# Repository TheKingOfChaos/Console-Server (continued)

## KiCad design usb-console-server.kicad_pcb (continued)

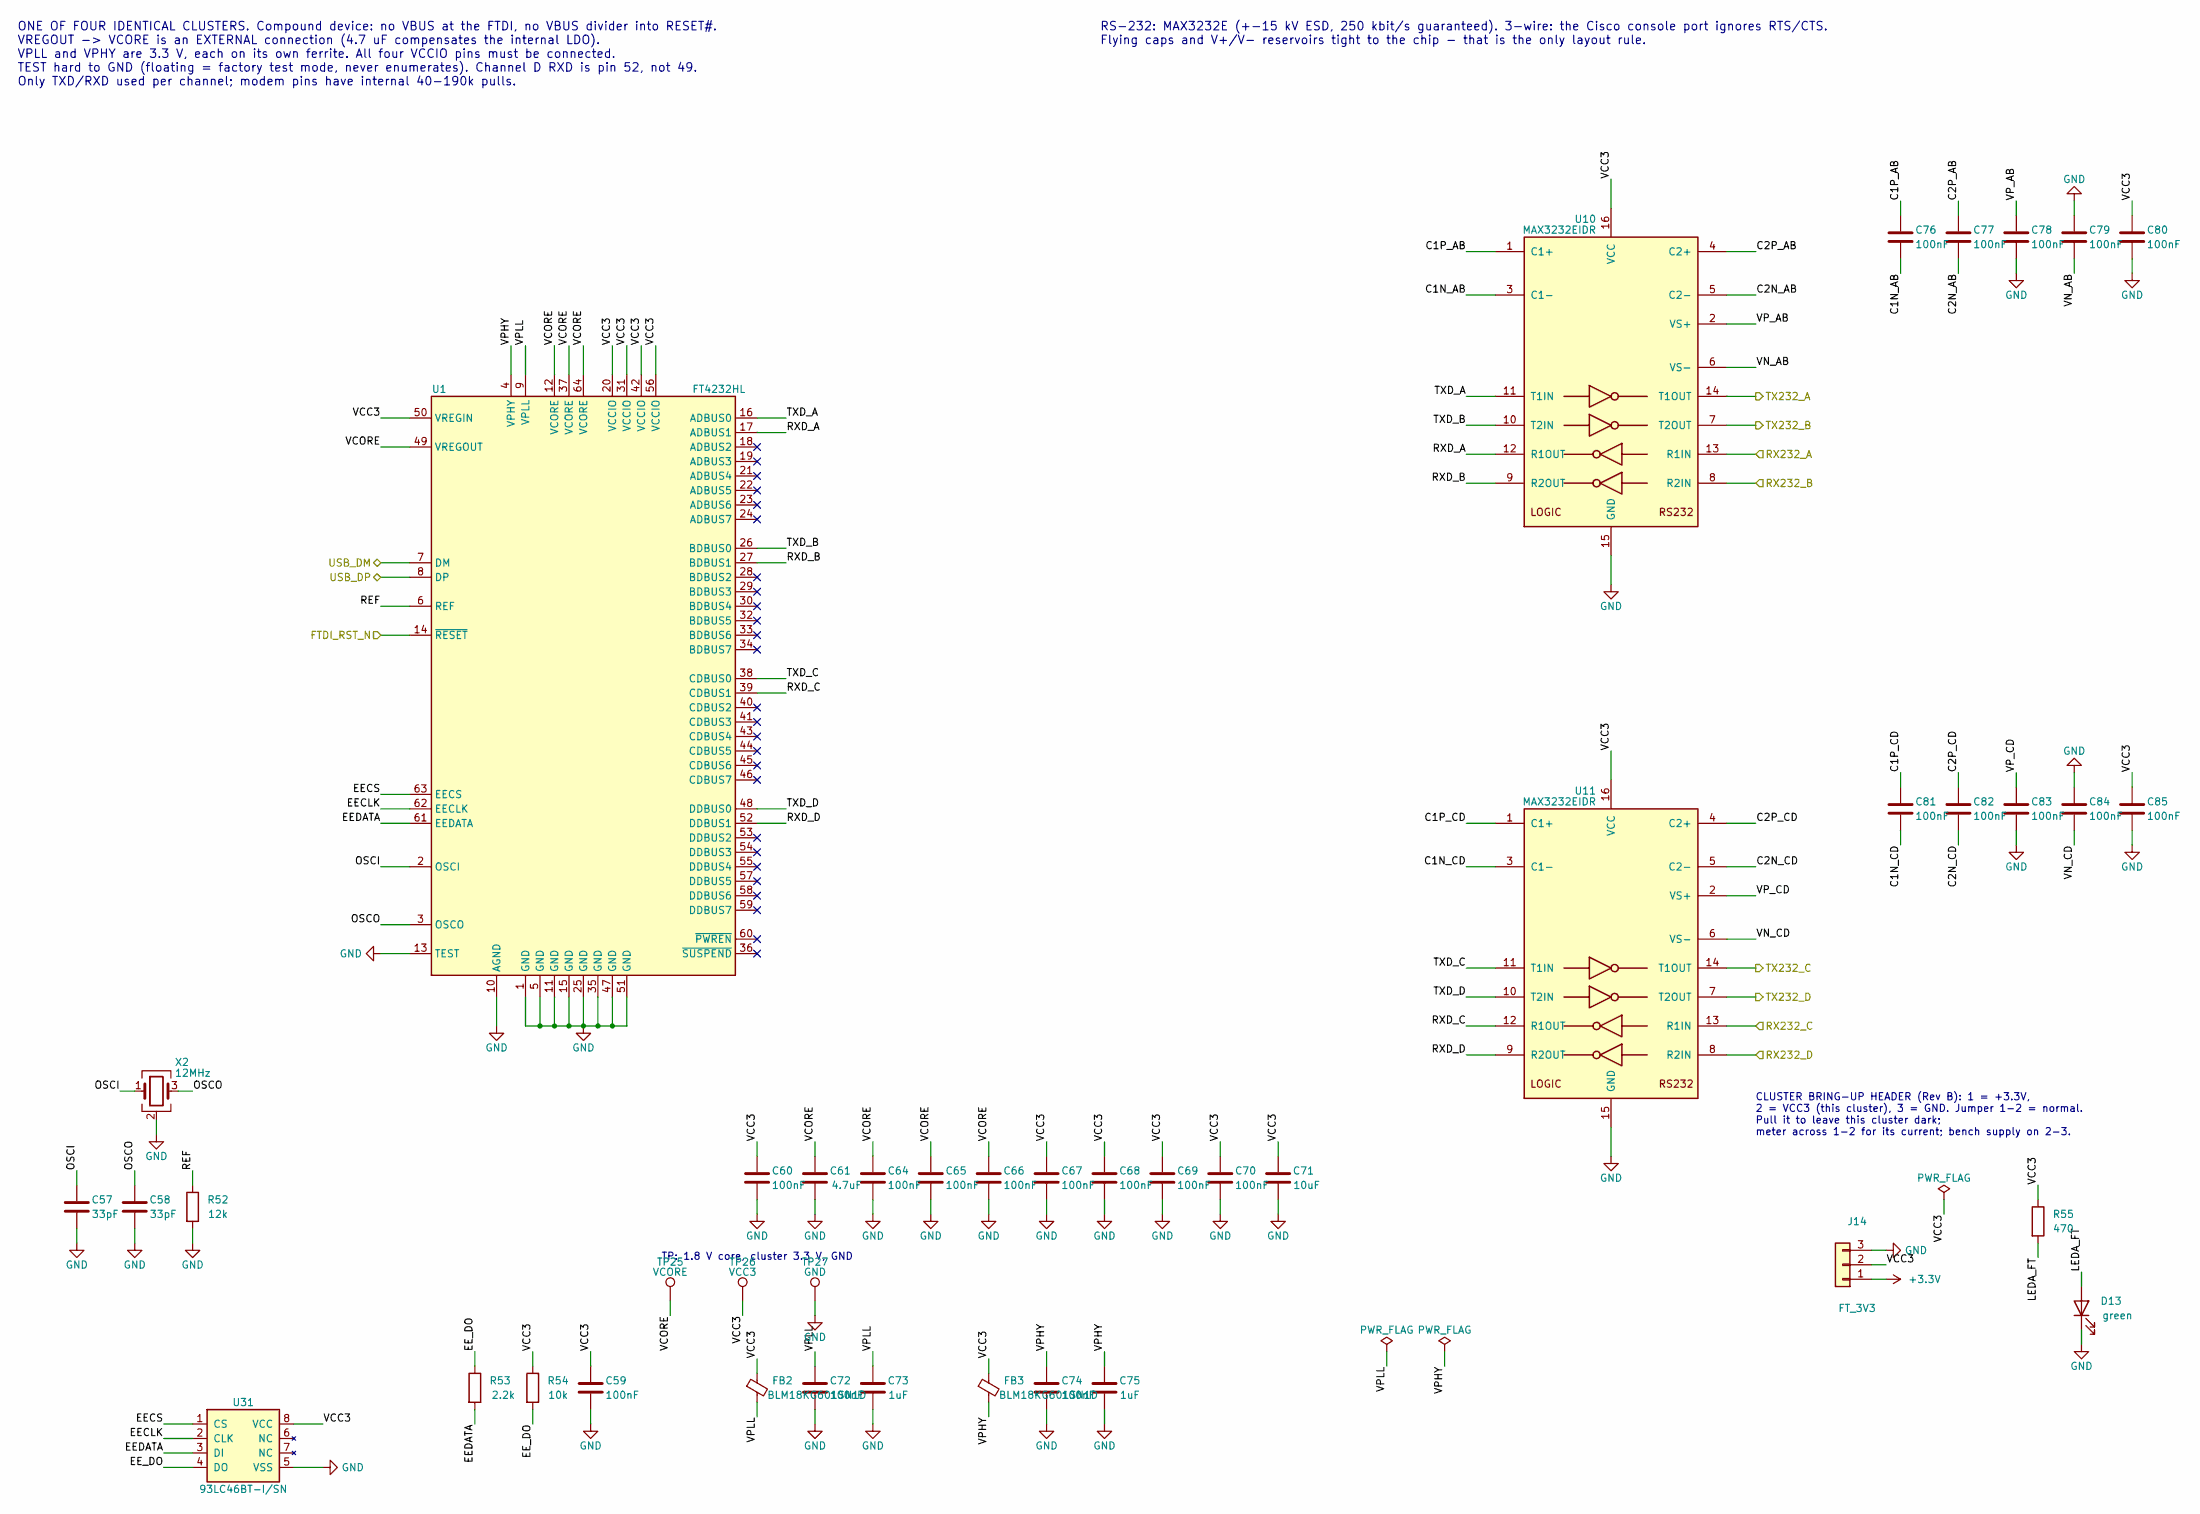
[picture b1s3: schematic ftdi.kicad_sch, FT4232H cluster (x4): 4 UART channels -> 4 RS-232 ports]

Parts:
C57, C58: 33pF; C_0603_1608Metric; LCSC C1663
C59, C60, C64, C65, C66, C67, C68, C69, C70, C72, C74, C76, C77, C78, C79, C80, C81, C82, C83, C84, C85: 100nF; C_0603_1608Metric; LCSC C14663
C61: 4.7uF; C_0805_2012Metric; LCSC C1779
C71: 10uF; C_0805_2012Metric; LCSC C15850
C73, C75: 1uF; C_0603_1608Metric; LCSC C29936
D13: green; LED_0603_1608Metric; LCSC C965805
FB2, FB3: BLM18KG601SN1D; L_0603_1608Metric; LCSC C85833
J14: FT_3V3; PinHeader_1x03_P2.54mm_Vertical; LCSC C49257
R52: 12k; R_0603_1608Metric; LCSC C22790
R53: 2.2k; R_0603_1608Metric; LCSC C4190
R54: 10k; R_0603_1608Metric; LCSC C25804
R55: 470; R_0603_1608Metric; LCSC C23179
TP25: VCORE; TestPoint_Pad_D1.5mm
TP26: VCC3; TestPoint_Pad_D1.5mm
TP27: GND; TestPoint_Pad_D1.5mm
U1: FT4232HL; LQFP-64_10x10mm_P0.5mm; LCSC C56742
U10, U11: MAX3232EIDR; SOIC-16_3.9x9.9mm_P1.27mm; LCSC C193666
U31: 93LC46BT-I/SN; SOIC-8_3.9x4.9mm_P1.27mm; LCSC C16253
X2: 12MHz; Crystal_SMD_3225-4Pin_3.2x2.5mm; LCSC C9002

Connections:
+3.3V: J14.1; also elsewhere on the board
/FT1/C1N_AB: C76.2, U10.3 (C1-)
/FT1/C1N_CD: C81.2, U11.3 (C1-)
/FT1/C1P_AB: C76.1, U10.1 (C1+)
/FT1/C1P_CD: C81.1, U11.1 (C1+)
/FT1/C2N_AB: C77.2, U10.5 (C2-)
/FT1/C2N_CD: C82.2, U11.5 (C2-)
/FT1/C2P_AB: C77.1, U10.4 (C2+)
/FT1/C2P_CD: C82.1, U11.4 (C2+)
/FT1/EECLK: U1.62 (EECLK), U31.2 (CLK)
/FT1/EECS: U1.63 (EECS), U31.1 (CS)
/FT1/EEDATA: R53.2, U1.61 (EEDATA), U31.3 (DI)
/FT1/EE_DO: R53.1, R54.2, U31.4 (DO)
/FT1/LEDA_FT: D13.2 (A), R55.2
/FT1/OSCI: C57.1, U1.2 (OSCI), X2.1
/FT1/OSCO: C58.1, U1.3 (OSCO), X2.3
/FT1/REF: R52.1, U1.6 (REF)
/FT1/RXD_A: U1.17 (ADBUS1), U10.12 (R1OUT)
/FT1/RXD_B: U1.27 (BDBUS1), U10.9 (R2OUT)
/FT1/RXD_C: U1.39 (CDBUS1), U11.12 (R1OUT)
/FT1/RXD_D: U1.52 (DDBUS1), U11.9 (R2OUT)
/FT1/TXD_A: U1.16 (ADBUS0), U10.11 (T1IN)
/FT1/TXD_B: U1.26 (BDBUS0), U10.10 (T2IN)
/FT1/TXD_C: U1.38 (CDBUS0), U11.11 (T1IN)
/FT1/TXD_D: U1.48 (DDBUS0), U11.10 (T2IN)
/FT1/VCC3: C59.1, C60.1, C67.1, C68.1, C69.1, C70.1, C71.1, C80.1, C85.1, FB2.1, FB3.1, J14.2, R54.1, R55.1, TP26.1, U1.20 (VCCIO), U1.31 (VCCIO), U1.42 (VCCIO), U1.50 (VREGIN), U1.56 (VCCIO), U10.16 (VCC), U11.16 (VCC), U31.8 (VCC)
/FT1/VCORE: C61.1, C64.1, C65.1, C66.1, TP25.1, U1.12 (VCORE), U1.37 (VCORE), U1.49 (VREGOUT), U1.64 (VCORE)
/FT1/VN_AB: C79.2, U10.6 (VS-)
/FT1/VN_CD: C84.2, U11.6 (VS-)
/FT1/VPHY: C74.1, C75.1, FB3.2, U1.4 (VPHY)
/FT1/VPLL: C72.1, C73.1, FB2.2, U1.9 (VPLL)
/FT1/VP_AB: C78.1, U10.2 (VS+)
/FT1/VP_CD: C83.1, U11.2 (VS+)
FTDI_RST_N: U1.14 (~RESET); also elsewhere on the board
GND: C57.2, C58.2, C59.2, C60.2, C61.2, C64.2, C65.2, C66.2, C67.2, C68.2, C69.2, C70.2, C71.2, C72.2, C73.2, C74.2, C75.2, C78.2, C79.1, C80.2, C83.2, C84.1, C85.2, D13.1 (K), J14.3, R52.2, TP27.1, U1.1 (GND), U1.5 (GND), U1.10 (AGND), U1.11 (GND), U1.13 (TEST), U1.15 (GND), U1.25 (GND), U1.35 (GND), U1.47 (GND), U1.51 (GND), U10.15 (GND), U11.15 (GND), U31.5 (VSS), X2.2 (G), X2.4 (G); also elsewhere on the board
P01_RXD: U10.13 (R1IN); also elsewhere on the board
P01_TXD: U10.14 (T1OUT); also elsewhere on the board
P02_RXD: U10.8 (R2IN); also elsewhere on the board
P02_TXD: U10.7 (T2OUT); also elsewhere on the board
P03_RXD: U11.13 (R1IN); also elsewhere on the board
P03_TXD: U11.14 (T1OUT); also elsewhere on the board
P04_RXD: U11.8 (R2IN); also elsewhere on the board
P04_TXD: U11.7 (T2OUT); also elsewhere on the board
USB_DN1_DM: U1.7 (DM); also elsewhere on the board
USB_DN1_DP: U1.8 (DP); also elsewhere on the board

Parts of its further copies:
C86, C87, C113, C114, C140, C141: 33pF; C_0603_1608Metric; LCSC C1663
C88, C89, C91, C92, C93, C94, C95, C96, C97, C99, C101, C103, C104, C105, C106, C107, C108, C109, C110, C111, C112, C115, C116, C118, C119, C120, C121, C122, C123, C124, C126, C128, C130, C131, C132, C133, C134, C135, C136, C137, C138, C139, C142, C143, C145, C146, C147, C148, C149, C150, C151, C153, C155, C157, C158, C159, C160, C161, C162, C163, C164, C165, C166: 100nF; C_0603_1608Metric; LCSC C14663
C90, C117, C144: 4.7uF; C_0805_2012Metric; LCSC C1779
C98, C125, C152: 10uF; C_0805_2012Metric; LCSC C15850
C100, C102, C127, C129, C154, C156: 1uF; C_0603_1608Metric; LCSC C29936
D14, D15, D16: green; LED_0603_1608Metric; LCSC C965805
FB4, FB5, FB6, FB7, FB8, FB9: BLM18KG601SN1D; L_0603_1608Metric; LCSC C85833
J15, J16, J17: FT_3V3; PinHeader_1x03_P2.54mm_Vertical; LCSC C49257
R56, R60, R64: 12k; R_0603_1608Metric; LCSC C22790
R57, R61, R65: 2.2k; R_0603_1608Metric; LCSC C4190
R58, R62, R66: 10k; R_0603_1608Metric; LCSC C25804
R59, R63, R67: 470; R_0603_1608Metric; LCSC C23179
TP28, TP31, TP34: VCORE; TestPoint_Pad_D1.5mm
TP29, TP32, TP35: VCC3; TestPoint_Pad_D1.5mm
TP30, TP33, TP36: GND; TestPoint_Pad_D1.5mm
U2, U3, U4: FT4232HL; LQFP-64_10x10mm_P0.5mm; LCSC C56742
U12, U13, U14, U15, U16, U17: MAX3232EIDR; SOIC-16_3.9x9.9mm_P1.27mm; LCSC C193666
U32, U33, U34: 93LC46BT-I/SN; SOIC-8_3.9x4.9mm_P1.27mm; LCSC C16253
X3, X4, X5: 12MHz; Crystal_SMD_3225-4Pin_3.2x2.5mm; LCSC C9002

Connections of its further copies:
+3.3V: J15.1, J16.1, J17.1; also elsewhere on the board
/FT2/C1N_AB: C103.2, U12.3 (C1-)
/FT2/C1N_CD: C108.2, U13.3 (C1-)
/FT2/C1P_AB: C103.1, U12.1 (C1+)
/FT2/C1P_CD: C108.1, U13.1 (C1+)
/FT2/C2N_AB: C104.2, U12.5 (C2-)
/FT2/C2N_CD: C109.2, U13.5 (C2-)
/FT2/C2P_AB: C104.1, U12.4 (C2+)
/FT2/C2P_CD: C109.1, U13.4 (C2+)
/FT2/EECLK: U2.62 (EECLK), U32.2 (CLK)
/FT2/EECS: U2.63 (EECS), U32.1 (CS)
/FT2/EEDATA: R57.2, U2.61 (EEDATA), U32.3 (DI)
/FT2/EE_DO: R57.1, R58.2, U32.4 (DO)
/FT2/LEDA_FT: D14.2 (A), R59.2
/FT2/OSCI: C86.1, U2.2 (OSCI), X3.1
/FT2/OSCO: C87.1, U2.3 (OSCO), X3.3
/FT2/REF: R56.1, U2.6 (REF)
/FT2/RXD_A: U2.17 (ADBUS1), U12.12 (R1OUT)
/FT2/RXD_B: U2.27 (BDBUS1), U12.9 (R2OUT)
/FT2/RXD_C: U2.39 (CDBUS1), U13.12 (R1OUT)
/FT2/RXD_D: U2.52 (DDBUS1), U13.9 (R2OUT)
/FT2/TXD_A: U2.16 (ADBUS0), U12.11 (T1IN)
/FT2/TXD_B: U2.26 (BDBUS0), U12.10 (T2IN)
/FT2/TXD_C: U2.38 (CDBUS0), U13.11 (T1IN)
/FT2/TXD_D: U2.48 (DDBUS0), U13.10 (T2IN)
/FT2/VCC3: C88.1, C89.1, C94.1, C95.1, C96.1, C97.1, C98.1, C107.1, C112.1, FB4.1, FB5.1, J15.2, R58.1, R59.1, TP29.1, U2.20 (VCCIO), U2.31 (VCCIO), U2.42 (VCCIO), U2.50 (VREGIN), U2.56 (VCCIO), U12.16 (VCC), U13.16 (VCC), U32.8 (VCC)
/FT2/VCORE: C90.1, C91.1, C92.1, C93.1, TP28.1, U2.12 (VCORE), U2.37 (VCORE), U2.49 (VREGOUT), U2.64 (VCORE)
/FT2/VN_AB: C106.2, U12.6 (VS-)
/FT2/VN_CD: C111.2, U13.6 (VS-)
/FT2/VPHY: C101.1, C102.1, FB5.2, U2.4 (VPHY)
/FT2/VPLL: C99.1, C100.1, FB4.2, U2.9 (VPLL)
/FT2/VP_AB: C105.1, U12.2 (VS+)
/FT2/VP_CD: C110.1, U13.2 (VS+)
/FT3/C1N_AB: C130.2, U14.3 (C1-)
/FT3/C1N_CD: C135.2, U15.3 (C1-)
/FT3/C1P_AB: C130.1, U14.1 (C1+)
/FT3/C1P_CD: C135.1, U15.1 (C1+)
/FT3/C2N_AB: C131.2, U14.5 (C2-)
/FT3/C2N_CD: C136.2, U15.5 (C2-)
/FT3/C2P_AB: C131.1, U14.4 (C2+)
/FT3/C2P_CD: C136.1, U15.4 (C2+)
/FT3/EECLK: U3.62 (EECLK), U33.2 (CLK)
/FT3/EECS: U3.63 (EECS), U33.1 (CS)
/FT3/EEDATA: R61.2, U3.61 (EEDATA), U33.3 (DI)
/FT3/EE_DO: R61.1, R62.2, U33.4 (DO)
/FT3/LEDA_FT: D15.2 (A), R63.2
/FT3/OSCI: C113.1, U3.2 (OSCI), X4.1
/FT3/OSCO: C114.1, U3.3 (OSCO), X4.3
/FT3/REF: R60.1, U3.6 (REF)
/FT3/RXD_A: U3.17 (ADBUS1), U14.12 (R1OUT)
/FT3/RXD_B: U3.27 (BDBUS1), U14.9 (R2OUT)
/FT3/RXD_C: U3.39 (CDBUS1), U15.12 (R1OUT)
/FT3/RXD_D: U3.52 (DDBUS1), U15.9 (R2OUT)
/FT3/TXD_A: U3.16 (ADBUS0), U14.11 (T1IN)
/FT3/TXD_B: U3.26 (BDBUS0), U14.10 (T2IN)
/FT3/TXD_C: U3.38 (CDBUS0), U15.11 (T1IN)
/FT3/TXD_D: U3.48 (DDBUS0), U15.10 (T2IN)
/FT3/VCC3: C115.1, C116.1, C121.1, C122.1, C123.1, C124.1, C125.1, C134.1, C139.1, FB6.1, FB7.1, J16.2, R62.1, R63.1, TP32.1, U3.20 (VCCIO), U3.31 (VCCIO), U3.42 (VCCIO), U3.50 (VREGIN), U3.56 (VCCIO), U14.16 (VCC), U15.16 (VCC), U33.8 (VCC)
/FT3/VCORE: C117.1, C118.1, C119.1, C120.1, TP31.1, U3.12 (VCORE), U3.37 (VCORE), U3.49 (VREGOUT), U3.64 (VCORE)
/FT3/VN_AB: C133.2, U14.6 (VS-)
/FT3/VN_CD: C138.2, U15.6 (VS-)
/FT3/VPHY: C128.1, C129.1, FB7.2, U3.4 (VPHY)
/FT3/VPLL: C126.1, C127.1, FB6.2, U3.9 (VPLL)
/FT3/VP_AB: C132.1, U14.2 (VS+)
/FT3/VP_CD: C137.1, U15.2 (VS+)
/FT4/C1N_AB: C157.2, U16.3 (C1-)
/FT4/C1N_CD: C162.2, U17.3 (C1-)
/FT4/C1P_AB: C157.1, U16.1 (C1+)
/FT4/C1P_CD: C162.1, U17.1 (C1+)
/FT4/C2N_AB: C158.2, U16.5 (C2-)
/FT4/C2N_CD: C163.2, U17.5 (C2-)
/FT4/C2P_AB: C158.1, U16.4 (C2+)
/FT4/C2P_CD: C163.1, U17.4 (C2+)
/FT4/EECLK: U4.62 (EECLK), U34.2 (CLK)
/FT4/EECS: U4.63 (EECS), U34.1 (CS)
/FT4/EEDATA: R65.2, U4.61 (EEDATA), U34.3 (DI)
/FT4/EE_DO: R65.1, R66.2, U34.4 (DO)
/FT4/LEDA_FT: D16.2 (A), R67.2
/FT4/OSCI: C140.1, U4.2 (OSCI), X5.1
/FT4/OSCO: C141.1, U4.3 (OSCO), X5.3
/FT4/REF: R64.1, U4.6 (REF)
/FT4/RXD_A: U4.17 (ADBUS1), U16.12 (R1OUT)
/FT4/RXD_B: U4.27 (BDBUS1), U16.9 (R2OUT)
/FT4/RXD_C: U4.39 (CDBUS1), U17.12 (R1OUT)
/FT4/RXD_D: U4.52 (DDBUS1), U17.9 (R2OUT)
/FT4/TXD_A: U4.16 (ADBUS0), U16.11 (T1IN)
/FT4/TXD_B: U4.26 (BDBUS0), U16.10 (T2IN)
/FT4/TXD_C: U4.38 (CDBUS0), U17.11 (T1IN)
/FT4/TXD_D: U4.48 (DDBUS0), U17.10 (T2IN)
/FT4/VCC3: C142.1, C143.1, C148.1, C149.1, C150.1, C151.1, C152.1, C161.1, C166.1, FB8.1, FB9.1, J17.2, R66.1, R67.1, TP35.1, U4.20 (VCCIO), U4.31 (VCCIO), U4.42 (VCCIO), U4.50 (VREGIN), U4.56 (VCCIO), U16.16 (VCC), U17.16 (VCC), U34.8 (VCC)
/FT4/VCORE: C144.1, C145.1, C146.1, C147.1, TP34.1, U4.12 (VCORE), U4.37 (VCORE), U4.49 (VREGOUT), U4.64 (VCORE)
/FT4/VN_AB: C160.2, U16.6 (VS-)
/FT4/VN_CD: C165.2, U17.6 (VS-)
/FT4/VPHY: C155.1, C156.1, FB9.2, U4.4 (VPHY)
/FT4/VPLL: C153.1, C154.1, FB8.2, U4.9 (VPLL)
/FT4/VP_AB: C159.1, U16.2 (VS+)
/FT4/VP_CD: C164.1, U17.2 (VS+)
FTDI_RST_N: U2.14 (~RESET), U3.14 (~RESET), U4.14 (~RESET); also elsewhere on the board
GND: C86.2, C87.2, C88.2, C89.2, C90.2, C91.2, C92.2, C93.2, C94.2, C95.2, C96.2, C97.2, C98.2, C99.2, C100.2, C101.2, C102.2, C105.2, C106.1, C107.2, C110.2, C111.1, C112.2, C113.2, C114.2, C115.2, C116.2, C117.2, C118.2, C119.2, C120.2, C121.2, C122.2, C123.2, C124.2, C125.2, C126.2, C127.2, C128.2, C129.2, C132.2, C133.1, C134.2, C137.2, C138.1, C139.2, C140.2, C141.2, C142.2, C143.2, C144.2, C145.2, C146.2, C147.2, C148.2, C149.2, C150.2, C151.2, C152.2, C153.2, C154.2, C155.2, C156.2, C159.2, C160.1, C161.2, C164.2, C165.1, C166.2, D14.1 (K), D15.1 (K), D16.1 (K), J15.3, J16.3, J17.3, R56.2, R60.2, R64.2, TP30.1, TP33.1, TP36.1, U2.1 (GND), U2.5 (GND), U2.10 (AGND), U2.11 (GND), U2.13 (TEST), U2.15 (GND), U2.25 (GND), U2.35 (GND), U2.47 (GND), U2.51 (GND), U3.1 (GND), U3.5 (GND), U3.10 (AGND), U3.11 (GND), U3.13 (TEST), U3.15 (GND), U3.25 (GND), U3.35 (GND), U3.47 (GND), U3.51 (GND), U4.1 (GND), U4.5 (GND), U4.10 (AGND), U4.11 (GND), U4.13 (TEST), U4.15 (GND), U4.25 (GND), U4.35 (GND), U4.47 (GND), U4.51 (GND), U12.15 (GND), U13.15 (GND), U14.15 (GND), U15.15 (GND), U16.15 (GND), U17.15 (GND), U32.5 (VSS), U33.5 (VSS), U34.5 (VSS), X3.2 (G), X3.4 (G), X4.2 (G), X4.4 (G), X5.2 (G), X5.4 (G); also elsewhere on the board
P05_RXD: U12.13 (R1IN); also elsewhere on the board
P05_TXD: U12.14 (T1OUT); also elsewhere on the board
P06_RXD: U12.8 (R2IN); also elsewhere on the board
P06_TXD: U12.7 (T2OUT); also elsewhere on the board
P07_RXD: U13.13 (R1IN); also elsewhere on the board
P07_TXD: U13.14 (T1OUT); also elsewhere on the board
P08_RXD: U13.8 (R2IN); also elsewhere on the board
P08_TXD: U13.7 (T2OUT); also elsewhere on the board
P09_RXD: U14.13 (R1IN); also elsewhere on the board
P09_TXD: U14.14 (T1OUT); also elsewhere on the board
P10_RXD: U14.8 (R2IN); also elsewhere on the board
P10_TXD: U14.7 (T2OUT); also elsewhere on the board
P11_RXD: U15.13 (R1IN); also elsewhere on the board
P11_TXD: U15.14 (T1OUT); also elsewhere on the board
P12_RXD: U15.8 (R2IN); also elsewhere on the board
P12_TXD: U15.7 (T2OUT); also elsewhere on the board
P13_RXD: U16.13 (R1IN); also elsewhere on the board
P13_TXD: U16.14 (T1OUT); also elsewhere on the board
P14_RXD: U16.8 (R2IN); also elsewhere on the board
P14_TXD: U16.7 (T2OUT); also elsewhere on the board
P15_RXD: U17.13 (R1IN); also elsewhere on the board
P15_TXD: U17.14 (T1OUT); also elsewhere on the board
P16_RXD: U17.8 (R2IN); also elsewhere on the board
P16_TXD: U17.7 (T2OUT); also elsewhere on the board
USB_DN2_DM: U2.7 (DM); also elsewhere on the board
USB_DN2_DP: U2.8 (DP); also elsewhere on the board
USB_DN3_DM: U3.7 (DM); also elsewhere on the board
USB_DN3_DP: U3.8 (DP); also elsewhere on the board
USB_DN4_DM: U4.7 (DM); also elsewhere on the board
USB_DN4_DP: U4.8 (DP); also elsewhere on the board

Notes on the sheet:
TP: 1.8 V core, cluster 3.3 V, GND
CLUSTER BRING-UP HEADER (Rev B): 1 = +3.3V, 2 = VCC3 (this cluster), 3 = GND. Jumper 1-2 = normal. Pull it to leave this cluster dark; meter across 1-2 for its current; bench supply on 2-3.
RS-232: MAX3232E (+-15 kV ESD, 250 kbit/s guaranteed). 3-wire: the Cisco console port ignores RTS/CTS. Flying caps and V+/V- reservoirs tight to the chip - that is the only layout rule.
ONE OF FOUR IDENTICAL CLUSTERS. Compound device: no VBUS at the FTDI, no VBUS divider into RESET#. VREGOUT -> VCORE is an EXTERNAL connection (4.7 uF compensates the internal LDO). VPLL and VPHY are 3.3 V, each on its own ferrite. All four VCCIO pins must be connected. TEST hard to GND (floating = 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

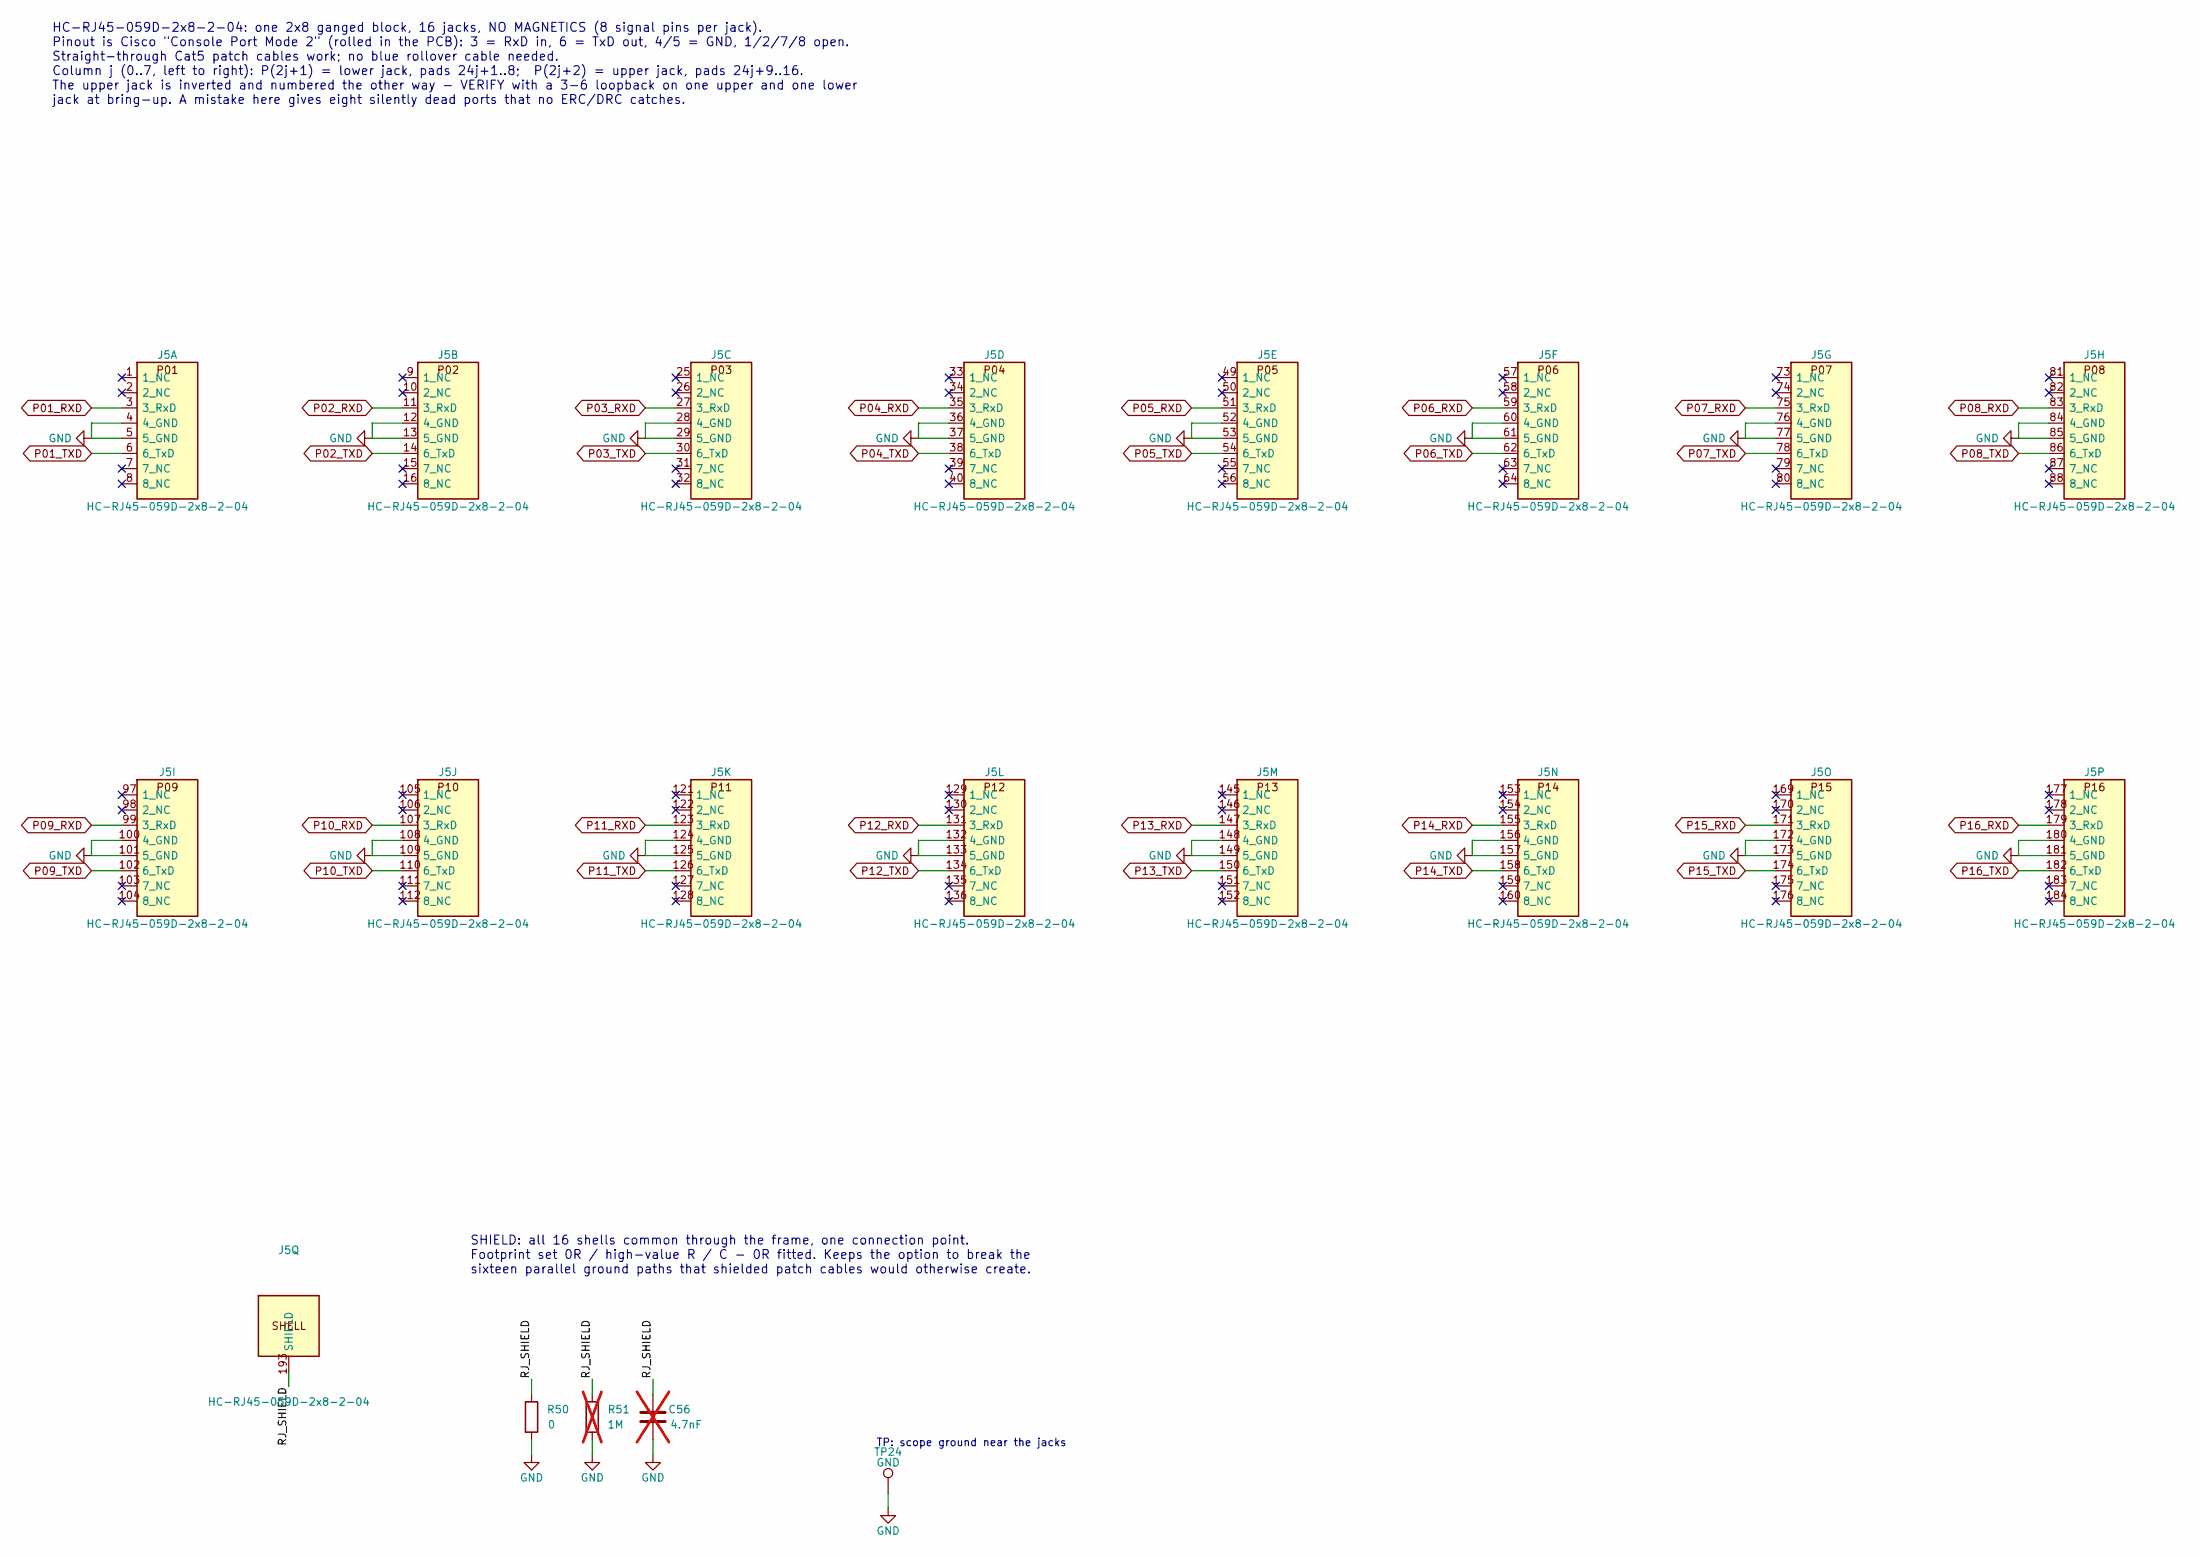
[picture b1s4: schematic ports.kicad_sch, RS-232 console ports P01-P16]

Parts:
C56: 4.7nF; C_0603_1608Metric; LCSC C53987; not fitted
J5: HC-RJ45-059D-2x8-2-04; RJ45_HC-RJ45-059D-2x8; LCSC C46261623
R50: 0; R_0603_1608Metric; LCSC C21189
R51: 1M; R_0603_1608Metric; LCSC C22935; not fitted
TP24: GND; TestPoint_Pad_D1.5mm

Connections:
/Ports/RJ_SHIELD: C56.1, J5.193 (SHIELD), J5.194 (SHIELD), J5.195 (SHIELD), J5.196 (SHIELD), R50.1, R51.1
GND: C56.2, J5.4 (4_GND), J5.5 (5_GND), J5.12 (4_GND), J5.13 (5_GND), J5.28 (4_GND), J5.29 (5_GND), J5.36 (4_GND), J5.37 (5_GND), J5.52 (4_GND), J5.53 (5_GND), J5.60 (4_GND), J5.61 (5_GND), J5.76 (4_GND), J5.77 (5_GND), J5.84 (4_GND), J5.85 (5_GND), J5.100 (4_GND), J5.101 (5_GND), J5.108 (4_GND), J5.109 (5_GND), J5.124 (4_GND), J5.125 (5_GND), J5.132 (4_GND), J5.133 (5_GND), J5.148 (4_GND), J5.149 (5_GND), J5.156 (4_GND), J5.157 (5_GND), J5.172 (4_GND), J5.173 (5_GND), J5.180 (4_GND), J5.181 (5_GND), R50.2, R51.2, TP24.1; also elsewhere on the board
P01_RXD: J5.3 (3_RxD); also elsewhere on the board
P01_TXD: J5.6 (6_TxD); also elsewhere on the board
P02_RXD: J5.11 (3_RxD); also elsewhere on the board
P02_TXD: J5.14 (6_TxD); also elsewhere on the board
P03_RXD: J5.27 (3_RxD); also elsewhere on the board
P03_TXD: J5.30 (6_TxD); also elsewhere on the board
P04_RXD: J5.35 (3_RxD); also elsewhere on the board
P04_TXD: J5.38 (6_TxD); also elsewhere on the board
P05_RXD: J5.51 (3_RxD); also elsewhere on the board
P05_TXD: J5.54 (6_TxD); also elsewhere on the board
P06_RXD: J5.59 (3_RxD); also elsewhere on the board
P06_TXD: J5.62 (6_TxD); also elsewhere on the board
P07_RXD: J5.75 (3_RxD); also elsewhere on the board
P07_TXD: J5.78 (6_TxD); also elsewhere on the board
P08_RXD: J5.83 (3_RxD); also elsewhere on the board
P08_TXD: J5.86 (6_TxD); also elsewhere on the board
P09_RXD: J5.99 (3_RxD); also elsewhere on the board
P09_TXD: J5.102 (6_TxD); also elsewhere on the board
P10_RXD: J5.107 (3_RxD); also elsewhere on the board
P10_TXD: J5.110 (6_TxD); also elsewhere on the board
P11_RXD: J5.123 (3_RxD); also elsewhere on the board
P11_TXD: J5.126 (6_TxD); also elsewhere on the board
P12_RXD: J5.131 (3_RxD); also elsewhere on the board
P12_TXD: J5.134 (6_TxD); also elsewhere on the board
P13_RXD: J5.147 (3_RxD); also elsewhere on the board
P13_TXD: J5.150 (6_TxD); also elsewhere on the board
P14_RXD: J5.155 (3_RxD); also elsewhere on the board
P14_TXD: J5.158 (6_TxD); also elsewhere on the board
P15_RXD: J5.171 (3_RxD); also elsewhere on the board
P15_TXD: J5.174 (6_TxD); also elsewhere on the board
P16_RXD: J5.179 (3_RxD); also elsewhere on the board
P16_TXD: J5.182 (6_TxD); also elsewhere on the board

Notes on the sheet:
HC-RJ45-059D-2x8-2-04: one 2x8 ganged block, 16 jacks, NO MAGNETICS (8 signal pins per jack). Pinout is Cisco "Console Port Mode 2" (rolled in the PCB): 3 = RxD in, 6 = TxD out, 4/5 = GND, 1/2/7/8 open. Straight-through Cat5 patch cables work; no blue rollover cable needed. Column j (0..7, left to 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
TP: scope ground near the jacks
SHIELD: all 16 shells common through the frame, one connection point. Footprint set 0R / high-value R / C - 0R fitted. Keeps the option to break the sixteen parallel ground paths that shielded patch cables would otherwise create.

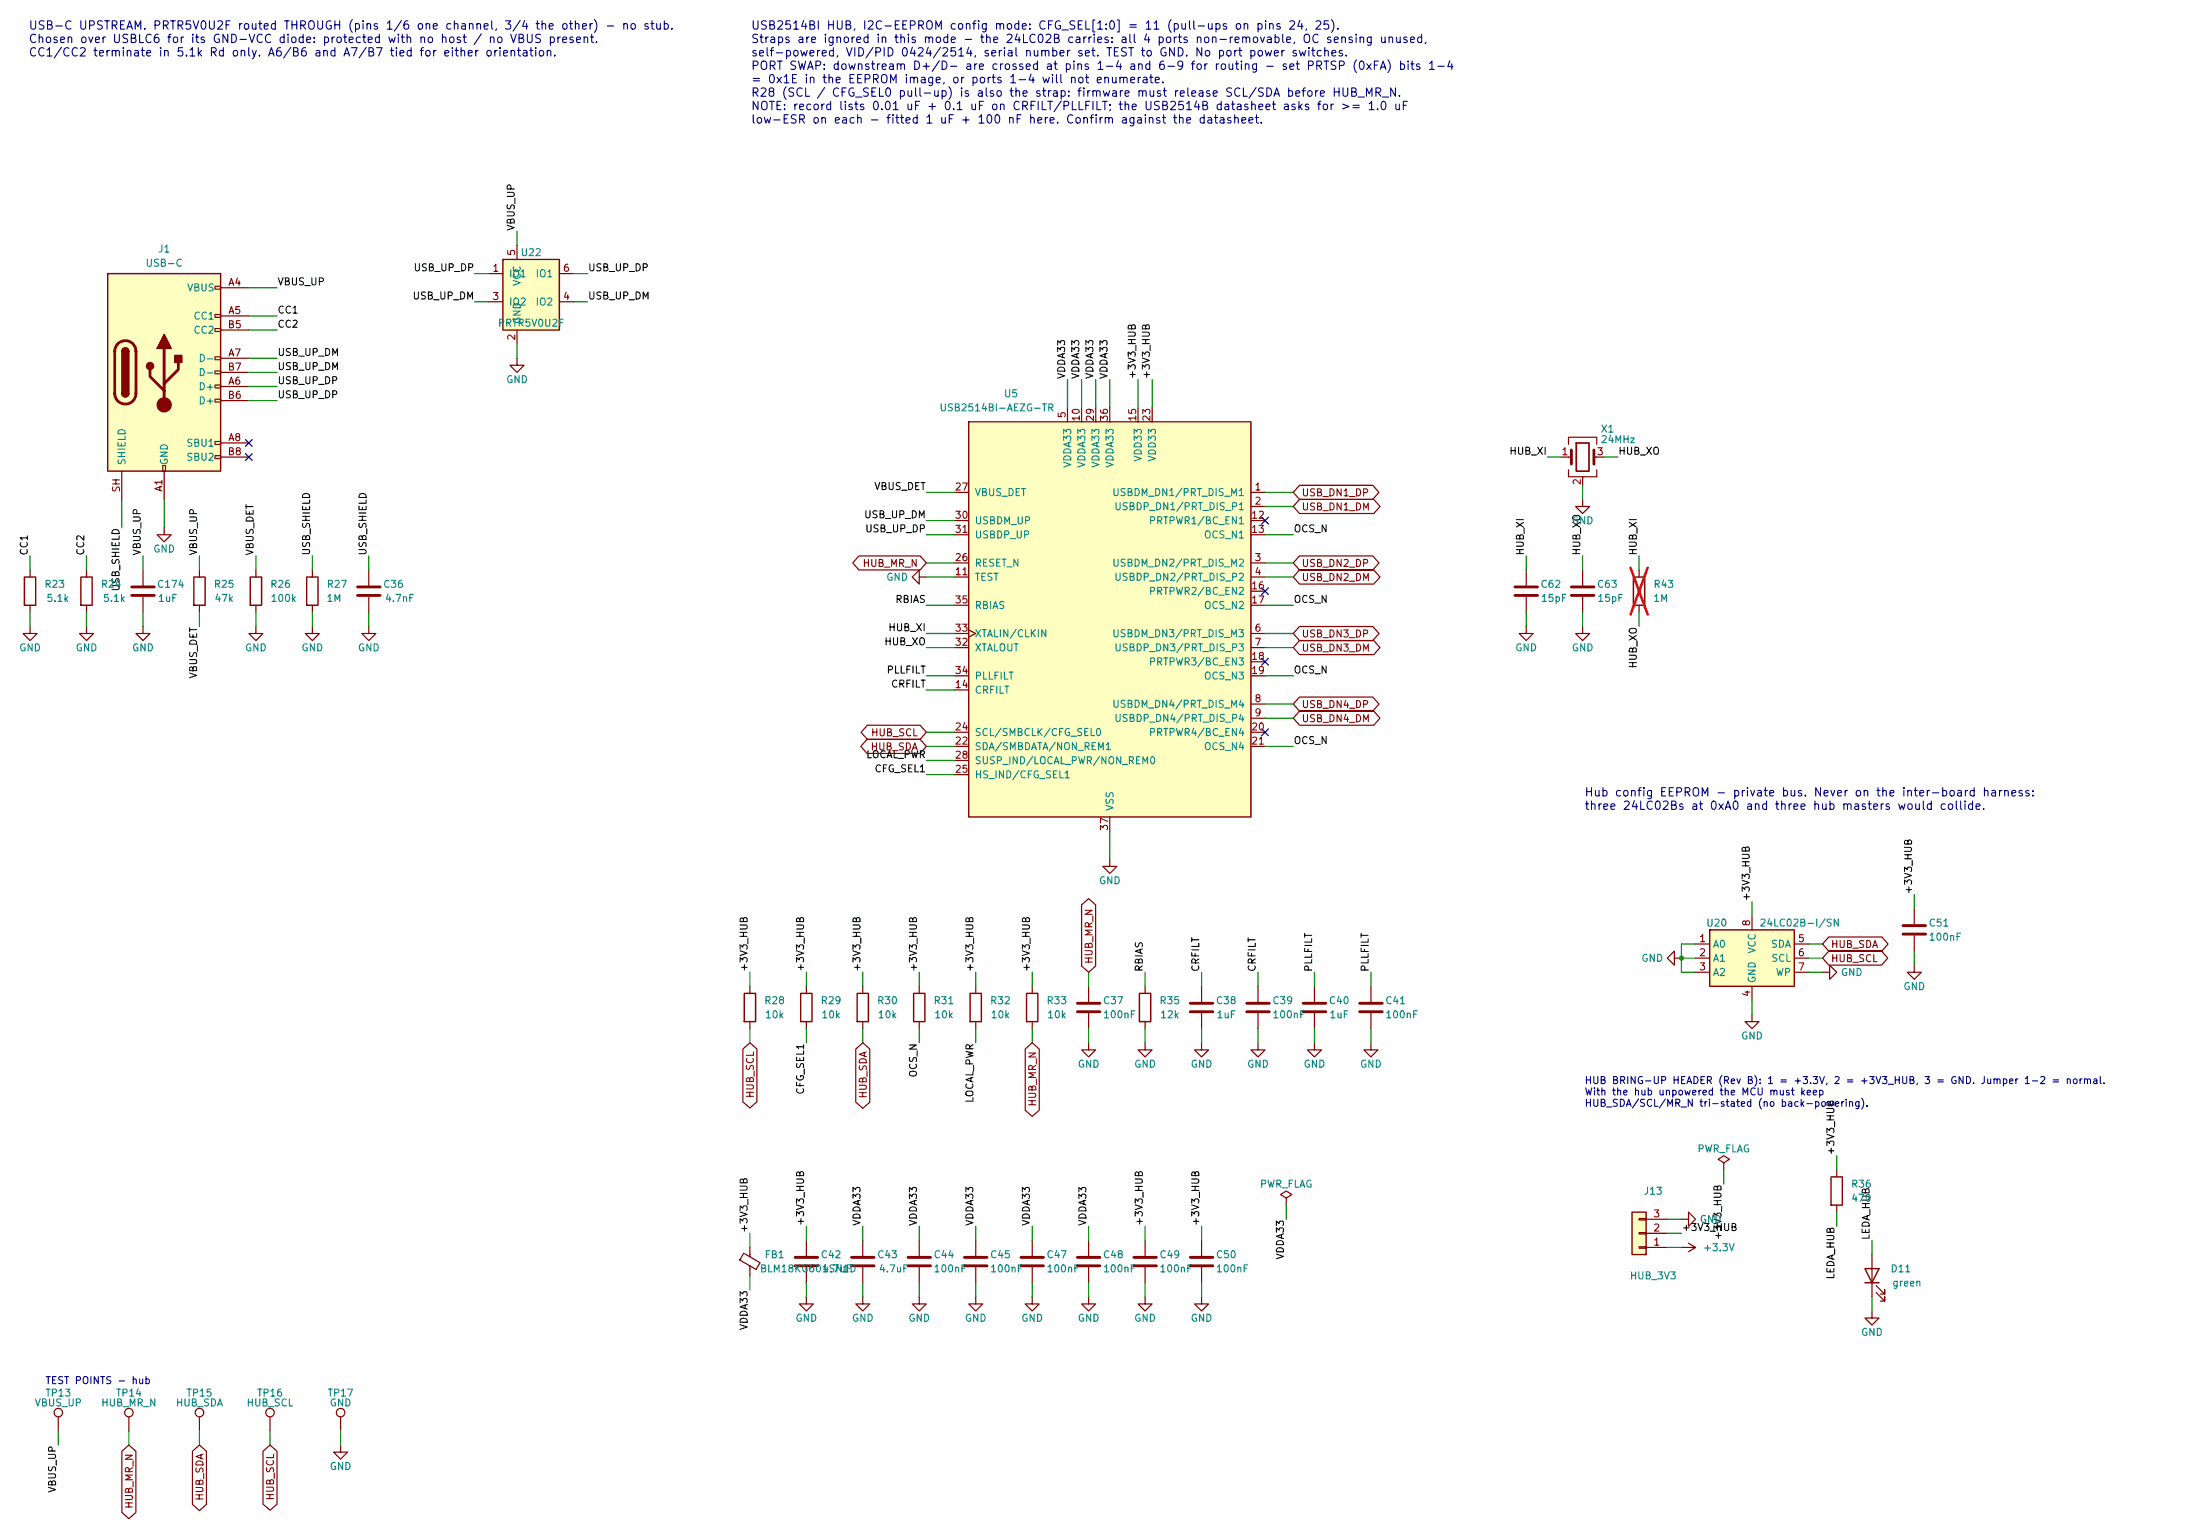
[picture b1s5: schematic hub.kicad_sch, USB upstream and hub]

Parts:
C36: 4.7nF; C_0603_1608Metric; LCSC C53987
C37, C39, C41, C44, C45, C47, C48, C49, C50, C51: 100nF; C_0603_1608Metric; LCSC C14663
C38, C40: 1uF; C_0603_1608Metric; LCSC C29936
C42, C43: 4.7uF; C_0805_2012Metric; LCSC C1779
C62, C63: 15pF; C_0603_1608Metric; LCSC C1644
C174: 1uF; C_0805_2012Metric; LCSC C91185
D11: green; LED_0603_1608Metric; LCSC C965805
FB1: BLM18KG601SN1D; L_0603_1608Metric; LCSC C85833
J1: USB-C; USB_C_Receptacle_HRO_TYPE-C-31-M-12; LCSC C165948
J13: HUB_3V3; PinHeader_1x03_P2.54mm_Vertical; LCSC C49257
R23, R24: 5.1k; R_0603_1608Metric; LCSC C23186
R25: 47k; R_0603_1608Metric; LCSC C111134
R26: 100k; R_0603_1608Metric; LCSC C25803
R27: 1M; R_0603_1608Metric; LCSC C22935
R28, R29, R30, R31, R32, R33: 10k; R_0603_1608Metric; LCSC C25804
R35: 12k; R_0603_1608Metric; LCSC C22790
R36: 470; R_0603_1608Metric; LCSC C23179
R43: 1M; R_0603_1608Metric; LCSC C22935; not fitted
TP13: VBUS_UP; TestPoint_Pad_D1.5mm
TP14: HUB_MR_N; TestPoint_Pad_D1.0mm
TP15: HUB_SDA; TestPoint_Pad_D1.0mm
TP16: HUB_SCL; TestPoint_Pad_D1.0mm
TP17: GND; TestPoint_Pad_D1.5mm
U5: USB2514BI-AEZG-TR; QFN-36-1EP_6x6mm_P0.5mm_EP3.7x3.7mm; LCSC C58940
U20: 24LC02B-I/SN; SOIC-8_3.9x4.9mm_P1.27mm; LCSC C1348870
U22: PRTR5V0U2F; SOT886_L1.5-W1.0-P0.50-LS1.00-BL; LCSC C478118
X1: 24MHz; Crystal_SMD_3225-4Pin_3.2x2.5mm; LCSC C5444545

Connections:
+3.3V: J13.1; also elsewhere on the board
/USB hub/+3V3_HUB: C42.1, C49.1, C50.1, C51.1, FB1.1, J13.2, R28.1, R29.1, R30.1, R31.1, R32.1, R33.1, R36.1, U5.15 (VDD33), U5.23 (VDD33), U20.8 (VCC)
/USB hub/CC1: J1.A5 (CC1), R23.1
/USB hub/CC2: J1.B5 (CC2), R24.1
/USB hub/CFG_SEL1: R29.2, U5.25 (HS_IND/CFG_SEL1)
/USB hub/CRFILT: C38.1, C39.1, U5.14 (CRFILT)
/USB hub/HUB_XI: C62.1, R43.1, U5.33 (XTALIN/CLKIN), X1.1
/USB hub/HUB_XO: C63.1, R43.2, U5.32 (XTALOUT), X1.3
/USB hub/LEDA_HUB: D11.2 (A), R36.2
/USB hub/LOCAL_PWR: R32.2, U5.28 (SUSP_IND/LOCAL_PWR/NON_REM0)
/USB hub/OCS_N: R31.2, U5.13 (OCS_N1), U5.17 (OCS_N2), U5.19 (OCS_N3), U5.21 (OCS_N4)
/USB hub/PLLFILT: C40.1, C41.1, U5.34 (PLLFILT)
/USB hub/RBIAS: R35.1, U5.35 (RBIAS)
/USB hub/USB_SHIELD: C36.1, J1.SH (SHIELD), R27.1
/USB hub/USB_UP_DM: J1.A7 (D-), J1.B7 (D-), U5.30 (USBDM_UP), U22.3 (IO2), U22.4 (IO2)
/USB hub/USB_UP_DP: J1.A6 (D+), J1.B6 (D+), U5.31 (USBDP_UP), U22.1 (IO1), U22.6 (IO1)
/USB hub/VBUS_DET: R25.2, R26.1, U5.27 (VBUS_DET)
/USB hub/VBUS_UP: C174.1, J1.A4 (VBUS), J1.A9 (VBUS), J1.B4 (VBUS), J1.B9 (VBUS), R25.1, TP13.1, U22.5 (VCC)
/USB hub/VDDA33: C43.1, C44.1, C45.1, C47.1, C48.1, FB1.2, U5.5 (VDDA33), U5.10 (VDDA33), U5.29 (VDDA33), U5.36 (VDDA33)
GND: C36.2, C37.2, C38.2, C39.2, C40.2, C41.2, C42.2, C43.2, C44.2, C45.2, C47.2, C48.2, C49.2, C50.2, C51.2, C62.2, C63.2, C174.2, D11.1 (K), J1.A1 (GND), J1.A12 (GND), J1.B1 (GND), J1.B12 (GND), J13.3, R23.2, R24.2, R26.2, R27.2, R35.2, TP17.1, U5.11 (TEST), U5.37 (VSS), U20.1 (A0), U20.2 (A1), U20.3 (A2), U20.4 (GND), U20.7 (WP), U22.2 (GND), X1.2 (G), X1.4 (G); also elsewhere on the board
HUB_MR_N: C37.1, R33.2, TP14.1, U5.26 (RESET_N); also elsewhere on the board
HUB_SCL: R28.2, TP16.1, U5.24 (SCL/SMBCLK/CFG_SEL0), U20.6 (SCL); also elsewhere on the board
HUB_SDA: R30.2, TP15.1, U5.22 (SDA/SMBDATA/NON_REM1), U20.5 (SDA); also elsewhere on the board
USB_DN1_DM: U5.2 (USBDP_DN1/PRT_DIS_P1); also elsewhere on the board
USB_DN1_DP: U5.1 (USBDM_DN1/PRT_DIS_M1); also elsewhere on the board
USB_DN2_DM: U5.4 (USBDP_DN2/PRT_DIS_P2); also elsewhere on the board
USB_DN2_DP: U5.3 (USBDM_DN2/PRT_DIS_M2); also elsewhere on the board
USB_DN3_DM: U5.7 (USBDP_DN3/PRT_DIS_P3); also elsewhere on the board
USB_DN3_DP: U5.6 (USBDM_DN3/PRT_DIS_M3); also elsewhere on the board
USB_DN4_DM: U5.9 (USBDP_DN4/PRT_DIS_P4); also elsewhere on the board
USB_DN4_DP: U5.8 (USBDM_DN4/PRT_DIS_M4); also elsewhere on the board

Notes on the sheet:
USB2514BI HUB, I2C-EEPROM config mode: CFG_SEL[1:0] = 11 (pull-ups on pins 24, 25). Straps are ignored in this mode - the 24LC02B carries: all 4 ports non-removable, OC sensing unused, self-powered, VID/PID 0424/2514, serial number set. TEST to GND. No port power switches. PORT SWAP: downstream D+/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
TEST POINTS - hub
HUB BRING-UP HEADER (Rev B): 1 = +3.3V, 2 = +3V3_HUB, 3 = GND. Jumper 1-2 = normal. With the hub unpowered the MCU must keep HUB_SDA/SCL/MR_N tri-stated (no back-powering).
USB-C UPSTREAM. PRTR5V0U2F routed THROUGH (pins 1/6 one channel, 3/4 the other) - no stub. Chosen over USBLC6 for its GND-VCC diode: protected with no host / no VBUS present. CC1/CC2 terminate in 5.1k Rd only. A6/B6 and A7/B7 tied for either orientation.
Hub config EEPROM - private bus. Never on the inter-board harness: three 24LC02Bs at 0xA0 and three hub masters would collide.
